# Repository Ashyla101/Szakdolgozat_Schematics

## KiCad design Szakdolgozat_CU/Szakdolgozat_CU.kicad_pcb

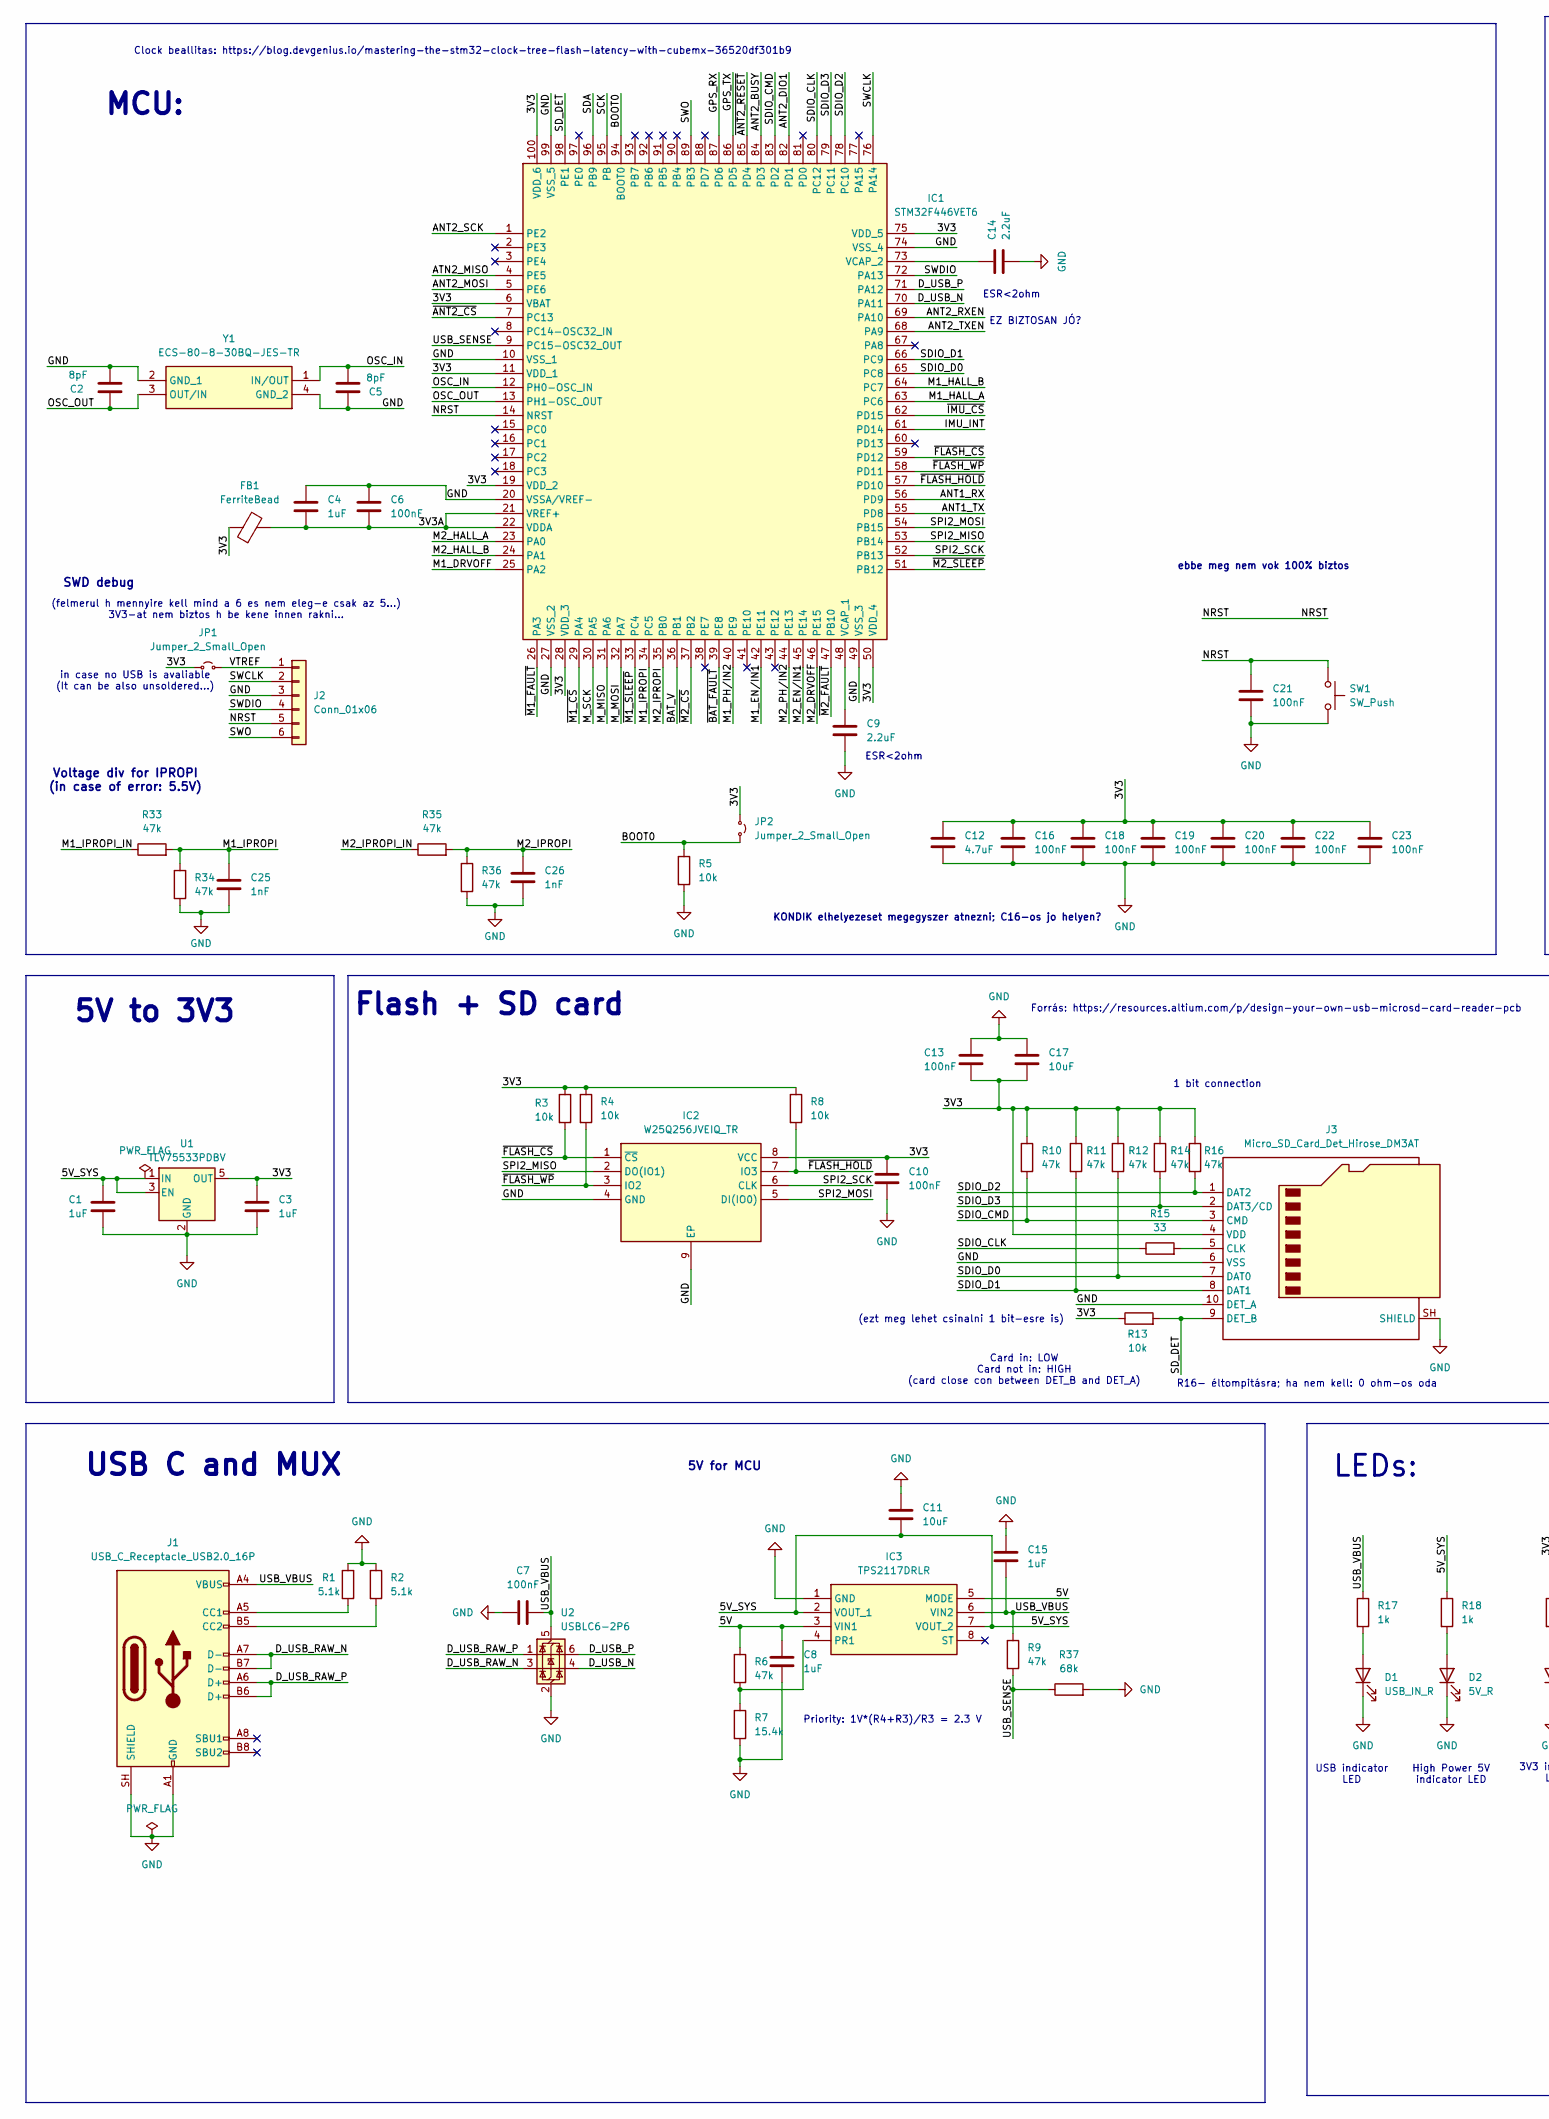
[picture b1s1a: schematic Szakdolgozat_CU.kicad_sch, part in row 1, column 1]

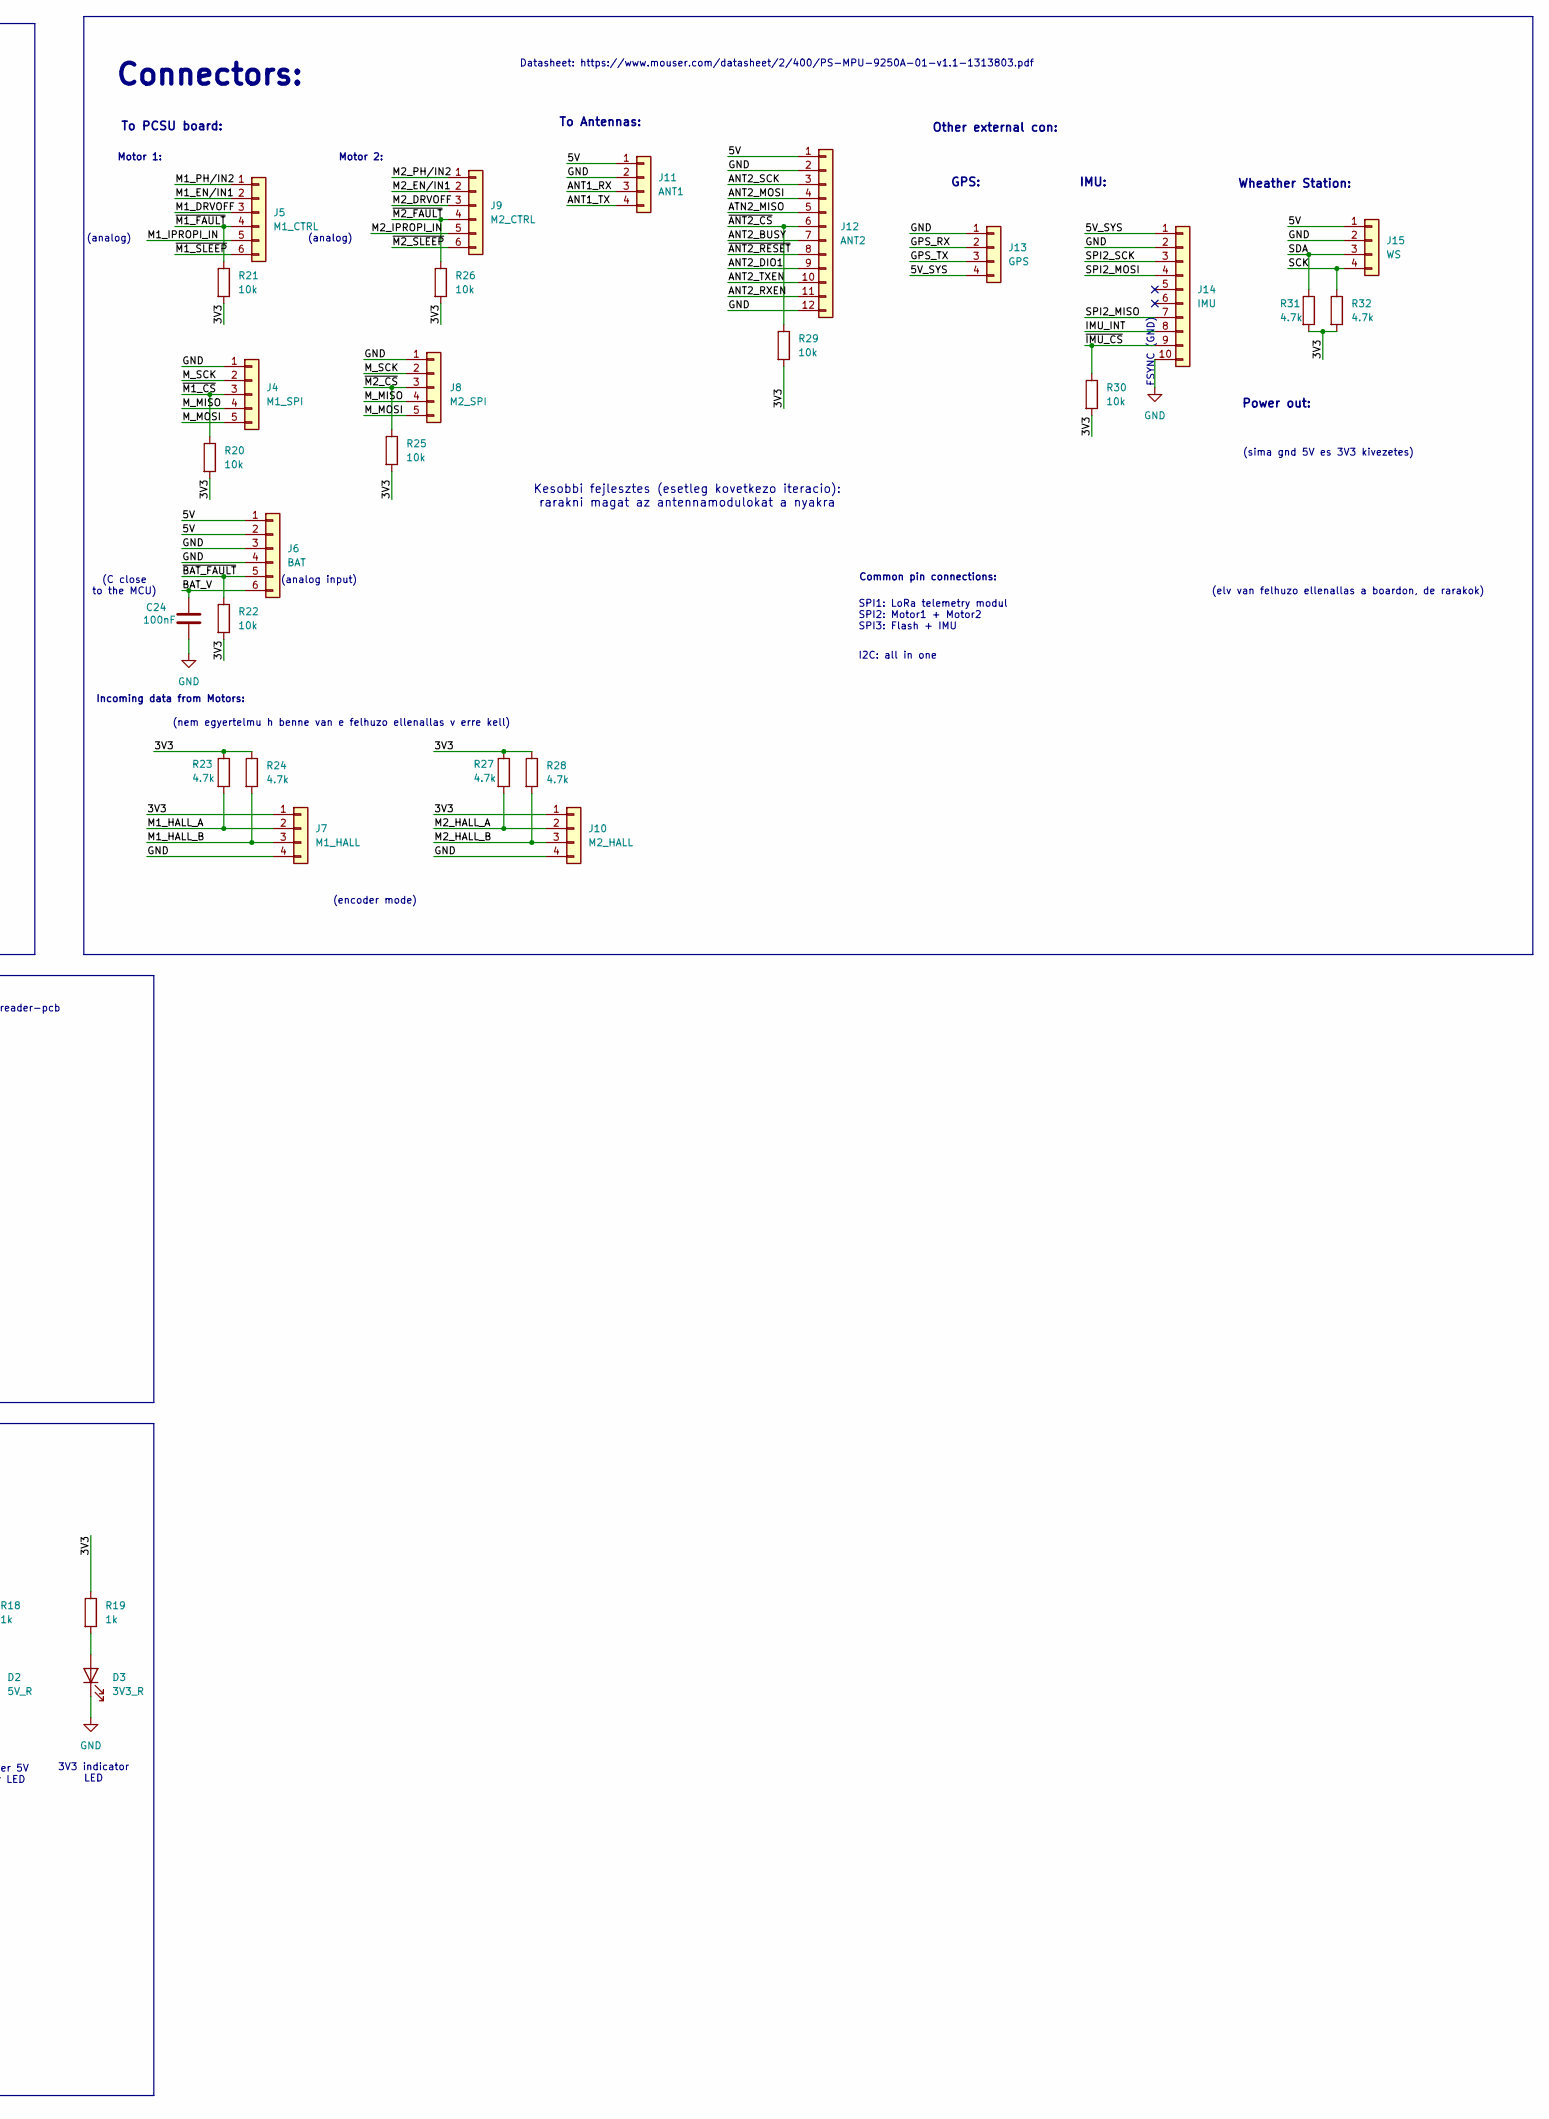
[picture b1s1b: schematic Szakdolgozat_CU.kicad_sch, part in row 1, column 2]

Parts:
C1, C3, C4, C8, C15: 1uF; C_0603_1608Metric_Pad1.08x0.95mm_HandSolder
C2, C5: 8pF; C_0603_1608Metric_Pad1.08x0.95mm_HandSolder
C6, C7, C10, C13, C16, C18, C19, C20, C21, C22, C23, C24: 100nF; C_0603_1608Metric_Pad1.08x0.95mm_HandSolder
C9, C14: 2.2uF; C_0603_1608Metric_Pad1.08x0.95mm_HandSolder
C11, C17: 10uF; C_0805_2012Metric_Pad1.18x1.45mm_HandSolder
C12: 4.7uF; C_0603_1608Metric_Pad1.08x0.95mm_HandSolder
C25, C26: 1nF; C_0603_1608Metric_Pad1.08x0.95mm_HandSolder
D1: USB_IN_R; LED_0603_1608Metric_Pad1.05x0.95mm_HandSolder
D2: 5V_R; LED_0603_1608Metric_Pad1.05x0.95mm_HandSolder
D3: 3V3_R; LED_0603_1608Metric_Pad1.05x0.95mm_HandSolder
FB1: FerriteBead; L_0603_1608Metric_Pad1.05x0.95mm_HandSolder
IC1: STM32F446VET6; QFP50P1600X1600X160-100N; Mouser Part Number 511-STM32F446VET6
IC2: W25Q256JVEIQ_TR; SON127P800X600X80-9N-D; Mouser Part Number 454-W25Q256JVEIQTR
IC3: TPS2117DRLR; SOTFL50P160X60-8N; Mouser Part Number 595-TPS2117DRLR
J1: USB_C_Receptacle_USB2.0_16P; USB_C_Receptacle_GCT_USB4105-xx-A_16P_TopMnt_Horizontal
J2: Conn_01x06; PinHeader_1x06_P2.54mm_Vertical
J3: Micro_SD_Card_Det_Hirose_DM3AT; microSD_HC_Hirose_DM3AT-SF-PEJM5
J4: M1_SPI; JST_XH_S5B-XH-A-1_1x05_P2.50mm_Horizontal
J5: M1_CTRL; JST_XH_S6B-XH-A-1_1x06_P2.50mm_Horizontal
J6: BAT; JST_XH_S6B-XH-A-1_1x06_P2.50mm_Horizontal
J7: M1_HALL; JST_XH_S4B-XH-A-1_1x04_P2.50mm_Horizontal
J8: M2_SPI; JST_XH_S5B-XH-A-1_1x05_P2.50mm_Horizontal
J9: M2_CTRL; JST_XH_S6B-XH-A-1_1x06_P2.50mm_Horizontal
J10: M2_HALL; JST_XH_S4B-XH-A-1_1x04_P2.50mm_Horizontal
J11: ANT1; JST_XH_S4B-XH-A-1_1x04_P2.50mm_Horizontal
J12: ANT2; JST_XH_S12B-XH-A-1_1x12_P2.50mm_Horizontal
J13: GPS; JST_XH_S4B-XH-A-1_1x04_P2.50mm_Horizontal
J14: IMU; JST_XH_S10B-XH-A_1x10_P2.50mm_Horizontal
J15: WS; JST_XH_S4B-XH-A-1_1x04_P2.50mm_Horizontal
JP1, JP2: Jumper_2_Small_Open; PinSocket_1x02_P2.54mm_Vertical
R1, R2: 5.1k; R_0603_1608Metric_Pad0.98x0.95mm_HandSolder
R3, R4, R5, R8, R13, R20, R21, R22, R25, R26, R29, R30: 10k; R_0603_1608Metric_Pad0.98x0.95mm_HandSolder
R6, R9, R10, R11, R12, R14, R16, R33, R34, R35, R36: 47k; R_0603_1608Metric_Pad0.98x0.95mm_HandSolder
R7: 15.4k; R_0603_1608Metric_Pad0.98x0.95mm_HandSolder
R15: 33; R_0603_1608Metric_Pad0.98x0.95mm_HandSolder
R17, R18, R19: 1k; R_0603_1608Metric_Pad0.98x0.95mm_HandSolder
R23, R24, R27, R28, R31, R32: 4.7k; R_0603_1608Metric_Pad0.98x0.95mm_HandSolder
R37: 68k; R_0603_1608Metric_Pad0.98x0.95mm_HandSolder
SW1: SW_Push; SW_Tactile_SPST_NO_Straight_CK_PTS636Sx25SMTRLFS
U1: TLV75533PDBV; SOT-23-5
U2: USBLC6-2P6; SOT-666
Y1: ECS-80-8-30BQ-JES-TR; ECS80830BQJESTR; Mouser Part Number 520-80-8-30BQ-JES-TR

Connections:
/3V3: C3.1, C10.1, C12.2, C13.2, C16.2, C17.2, C18.1, C19.1, C20.2, C22.2, C23.2, FB1.1, IC1.6 (VBAT), IC1.11 (VDD_1), IC1.19 (VDD_2), IC1.28 (VDD_3), IC1.50 (VDD_4), IC1.75 (VDD_5), IC1.100 (VDD_6), IC2.8 (VCC), J3.4 (VDD), J7.1, J10.1, JP1.1 (A), JP2.1 (A), R3.1, R4.1, R8.1, R10.1, R11.1, R12.1, R13.1, R14.1, R16.1, R19.1, R20.2, R21.2, R22.2, R23.1, R24.1, R25.2, R26.2, R27.1, R28.1, R29.2, R30.2, R31.2, R32.2, U1.5 (OUT)
/3V3A: C4.2, C6.2, FB1.2, IC1.21 (VREF+), IC1.22 (VDDA)
/5V: C8.1, IC3.3 (VIN1), IC3.5 (MODE), J6.1, J6.2, J11.1, J12.1, J15.1, R6.1
/5V_SYS: C1.1, C11.1, IC3.2 (VOUT_1), IC3.7 (VOUT_2), J13.4, J14.1, R18.1, U1.1 (IN), U1.3 (EN)
/ANT1_RX: IC1.56 (PD9), J11.3
/ANT1_TX: IC1.55 (PD8), J11.4
/ANT2_BUSY: IC1.84 (PD3), J12.7
/ANT2_DIO1: IC1.82 (PD1), J12.9
/ANT2_MOSI: IC1.5 (PE6), J12.4
/ANT2_RXEN: IC1.69 (PA10), J12.11
/ANT2_SCK: IC1.1 (PE2), J12.3
/ANT2_TXEN: IC1.68 (PA9), J12.10
/ATN2_MISO: IC1.4 (PE5), J12.5
/BAT_V: C24.1, IC1.36 (PB1), J6.6
/BOOT0: IC1.94 (BOOT0), JP2.2 (B), R5.1
/D_USB_N: IC1.70 (PA11), U2.4 (I/O2)
/D_USB_P: IC1.71 (PA12), U2.6 (I/O1)
/D_USB_RAW_N: J1.A7 (D-), J1.B7 (D-), U2.3 (I/O2)
/D_USB_RAW_P: J1.A6 (D+), J1.B6 (D+), U2.1 (I/O1)
/GPS_RX: IC1.87 (PD6), J13.2
/GPS_TX: IC1.86 (PD5), J13.3
/IMU_INT: IC1.61 (PD14), J14.8
/M1_DRVOFF: IC1.25 (PA2), J5.3
/M1_EN/IN1: IC1.42 (PE11), J5.2
/M1_HALL_A: IC1.63 (PC6), J7.2, R23.2
/M1_HALL_B: IC1.64 (PC7), J7.3, R24.2
/M1_IPROPI: C25.1, IC1.34 (PC5), R33.2, R34.2
/M1_IPROPI_IN: J5.5, R33.1
/M1_PH/IN2: IC1.40 (PE9), J5.1
/M2_DRVOFF: IC1.46 (PE15), J9.3
/M2_EN/IN1: IC1.45 (PE14), J9.2
/M2_HALL_A: IC1.23 (PA0), J10.2, R27.2
/M2_HALL_B: IC1.24 (PA1), J10.3, R28.2
/M2_IPROPI: C26.1, IC1.35 (PB0), R35.2, R36.1
/M2_IPROPI_IN: J9.5, R35.1
/M2_PH/IN2: IC1.44 (PE13), J9.1
/M_MISO: IC1.31 (PA6), J4.4, J8.4
/M_MOSI: IC1.32 (PA7), J4.5, J8.5
/M_SCK: IC1.30 (PA5), J4.2, J8.2
/NRST: C21.1, IC1.14 (NRST), J2.5, SW1.1
/OSC_IN: C5.2, IC1.12 (PH0-OSC_IN), Y1.1 (IN/OUT)
/OSC_OUT: C2.2, IC1.13 (PH1-OSC_OUT), Y1.3 (OUT/IN)
/SCK: IC1.95 (PB), J15.4, R32.1
/SDA: IC1.96 (PB9), J15.3, R31.1
/SDIO_CLK: IC1.80 (PC12), R15.1
/SDIO_CMD: IC1.83 (PD2), J3.3 (CMD), R10.2
/SDIO_D0: IC1.65 (PC8), J3.7 (DAT0), R12.2
/SDIO_D1: IC1.66 (PC9), J3.8 (DAT1), R11.2
/SDIO_D2: IC1.78 (PC10), J3.1 (DAT2), R16.2
/SDIO_D3: IC1.79 (PC11), J3.2 (DAT3/CD), R14.2
/SD_DET: IC1.98 (PE1), J3.9 (DET_B), R13.2
/SPI2_MISO: IC1.53 (PB14), IC2.2 (DO(IO1)), J14.7
/SPI2_MOSI: IC1.54 (PB15), IC2.5 (DI(IO0)), J14.4
/SPI2_SCK: IC1.52 (PB13), IC2.6 (CLK), J14.3
/SWCLK: IC1.76 (PA14), J2.2
/SWDIO: IC1.72 (PA13), J2.4
/SWO: IC1.89 (PB3), J2.6
/USB_SENSE: IC1.9 (PC15-OSC32_OUT), R9.2, R37.1
/USB_VBUS: C7.2, C15.2, IC3.6 (VIN2), J1.A4 (VBUS), J1.A9 (VBUS), J1.B4 (VBUS), J1.B9 (VBUS), R9.1, R17.1, U2.5 (VBUS)
/VTREF: J2.1, JP1.2 (B)
/~ANT2_CS: IC1.7 (PC13), J12.6, R29.1
/~ANT2_RESET: IC1.85 (PD4), J12.8
/~BAT_FAULT: IC1.39 (PE8), J6.5, R22.1
/~FLASH_CS: IC1.59 (PD12), IC2.1 (~CS), R3.2
/~FLASH_HOLD: IC1.57 (PD10), IC2.7 (IO3), R8.2
/~FLASH_WP: IC1.58 (PD11), IC2.3 (IO2), R4.2
/~IMU_CS: IC1.62 (PD15), J14.9, R30.1
/~M1_CS: IC1.29 (PA4), J4.3, R20.1
/~M1_FAULT: IC1.26 (PA3), J5.4, R21.1
/~M1_SLEEP: IC1.33 (PC4), J5.6
/~M2_CS: IC1.37 (PB2), J8.3, R25.1
/~M2_FAULT: IC1.47 (PB10), J9.4, R26.1
/~M2_SLEEP: IC1.51 (PB12), J9.6
GND: C1.2, C2.1, C3.2, C4.1, C5.1, C6.1, C7.1, C8.2, C9.1, C10.2, C11.2, C12.1, C13.1, C14.1, C15.1, C16.1, C17.1, C18.2, C19.2, C20.1, C21.2, C22.1, C23.1, C24.2, C25.2, C26.2, D1.1 (K), D2.1 (K), D3.1 (K), IC1.10 (VSS_1), IC1.20 (VSSA/VREF-), IC1.27 (VSS_2), IC1.49 (VSS_3), IC1.74 (VSS_4), IC1.99 (VSS_5), IC2.4 (GND), IC2.9 (EP), IC3.1 (GND), J1.A1 (GND), J1.A12 (GND), J1.B1 (GND), J1.B12 (GND), J1.SH (SHIELD), J2.3, J3.6 (VSS), J3.10 (DET_A), J3.SH (SHIELD), J4.1, J6.3, J6.4, J7.4, J8.1, J10.4, J11.2, J12.2, J12.12, J13.1, J14.2, J14.10, J15.2, R1.2, R2.1, R5.2, R7.2, R34.1, R36.2, R37.2, SW1.2, U1.2 (GND), U2.2 (GND), Y1.2 (GND_1), Y1.4 (GND_2)
unnamed: D1.2 (A), R17.2
unnamed: D2.2 (A), R18.2
unnamed: D3.2 (A), R19.2
unnamed: C9.2, IC1.48 (VCAP_1)
unnamed: C14.2, IC1.73 (VCAP_2)
unnamed: IC3.4 (PR1), R6.2, R7.1
unnamed: J1.A5 (CC1), R1.1
unnamed: J1.B5 (CC2), R2.2
unnamed: J3.5 (CLK), R15.2

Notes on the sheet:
Forrás: https://resources.altium.com/p/design-your-own-usb-microsd-card-reader-pcb
IMU:
Voltage div for IPROPI (in case of error: 5.5V)
Motor 1:
To Antennas:
Clock beallitas: https://blog.devgenius.io/mastering-the-stm32-clock-tree-flash-latency-with-cubemx-36520df301b9
Other external con:
Datasheet: https://www.mouser.com/datasheet/2/400/PS-MPU-9250A-01-v1.1-1313803.pdf
Wheather Station:
Incoming data from Motors:
USB indicator LED
(analog)
in case no USB is avaliable (It can be also unsoldered...)
EZ BIZTOSAN JÓ?
ESR<2ohm
Connectors:
SWD debug
USB C and MUX
(elv van felhuzo ellenallas a boardon, de rarakok)
FSYNC (GND)
MCU:
Priority: 1V*(R4+R3)/R3 = 2.3 V
GPS:
ebbe meg nem vok 100% biztos
R16- éltompitásra; ha nem kell: 0 ohm-os oda
KONDIK elhelyezeset megegyszer atnezni; C16-os jo helyen?
5V for MCU
Common pin connections:
Card in: LOW Card not in: HIGH (card close con between DET_B and DET_A)
Power out:
(C close to the MCU)
LEDs:
(sima gnd 5V es 3V3 kivezetes)
5V to 3V3
SPI1: LoRa telemetry modul SPI2: Motor1 + Motor2 SPI3: Flash + IMU
(encoder mode)
Motor 2:
(ezt meg lehet csinalni 1 bit-esre is)
I2C: all in one
(analog input)

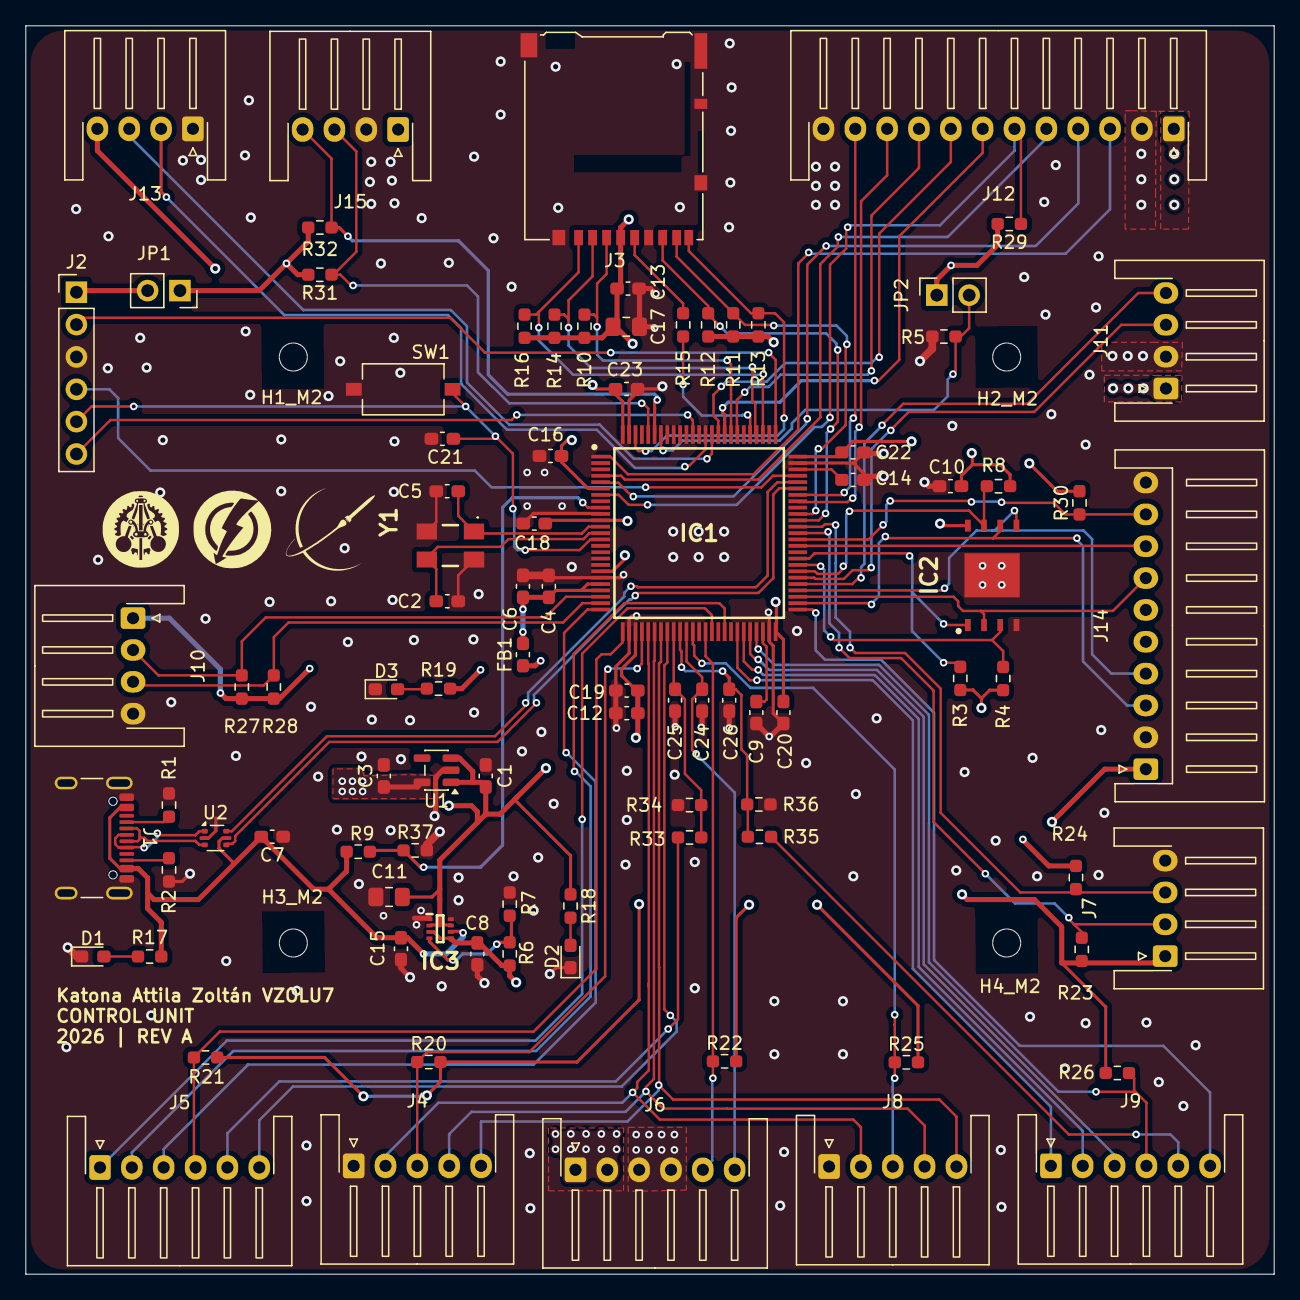
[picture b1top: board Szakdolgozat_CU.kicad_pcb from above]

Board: 4 copper layers, 98.0 x 98.0 mm, 95 parts (0 on the bottom side), 83 nets.

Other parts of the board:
H1_M2, H2_M2, H3_M2, H4_M2: MountingHole_2.2mm_M2

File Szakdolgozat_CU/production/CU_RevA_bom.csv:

Designator,Footprint,Quantity,Value,LCSC Part #
"C1, C15, C3, C4, C8",0603,5,1uF,
"C10, C13, C16, C18, C19, C20, C21, C22, C23, C24, C6, C7",0603,12,100nF,
"C11, C17",0805,2,10uF,
C12,0603,1,4.7uF,
"C14, C9",0603,2,2.2uF,
"C2, C5",0603,2,8pF,
"C25, C26",0603,2,1nF,
D1,0603,1,USB_IN_R,
D2,0603,1,5V_R,
D3,0603,1,3V3_R,
FB1,0603,1,FerriteBead,
IC1,QFP50P1600X1600X160-100N,1,STM32F446VET6,
IC2,SON127P800X600X80-9N-D,1,W25Q256JVEIQ_TR,
IC3,SOTFL50P160X60-8N,1,TPS2117DRLR,
J1,USB_C_Receptacle_GCT_USB4105-xx-A_16P_TopMnt_Horizontal,1,USB_C_Receptacle_USB2.0_16P,
J10,JST_XH_S4B-XH-A-1_1x04_P2.50mm_Horizontal,1,M2_HALL,
J11,JST_XH_S4B-XH-A-1_1x04_P2.50mm_Horizontal,1,ANT1,
J12,JST_XH_S12B-XH-A-1_1x12_P2.50mm_Horizontal,1,ANT2,
J13,JST_XH_S4B-XH-A-1_1x04_P2.50mm_Horizontal,1,GPS,
J14,JST_XH_S10B-XH-A_1x10_P2.50mm_Horizontal,1,IMU,
J15,JST_XH_S4B-XH-A-1_1x04_P2.50mm_Horizontal,1,WS,
J2,PinHeader_1x06_P2.54mm_Vertical,1,Conn_01x06,
J3,microSD_HC_Hirose_DM3AT-SF-PEJM5,1,Micro_SD_Card_Det_Hirose_DM3AT,
J4,JST_XH_S5B-XH-A-1_1x05_P2.50mm_Horizontal,1,M1_SPI,
J5,JST_XH_S6B-XH-A-1_1x06_P2.50mm_Horizontal,1,M1_CTRL,
J6,JST_XH_S6B-XH-A-1_1x06_P2.50mm_Horizontal,1,BAT,
J7,JST_XH_S4B-XH-A-1_1x04_P2.50mm_Horizontal,1,M1_HALL,
J8,JST_XH_S5B-XH-A-1_1x05_P2.50mm_Horizontal,1,M2_SPI,
J9,JST_XH_S6B-XH-A-1_1x06_P2.50mm_Horizontal,1,M2_CTRL,
"JP1, JP2",PinSocket_1x02_P2.54mm_Vertical,2,Jumper_2_Small_Open,
"R1, R2",0603,2,5.1k,
"R10, R11, R12, R14, R16, R33, R34, R35, R36, R6, R9",0603,11,47k,
"R13, R20, R21, R22, R25, R26, R29, R3, R30, R4, R5, R8",0603,12,10k,
R15,0603,1,33,
"R17, R18, R19",0603,3,1k,
"R23, R24, R27, R28, R31, R32",0603,6,4.7k,
R37,0603,1,68k,
R7,0603,1,15.4k,
SW1,SW_Tactile_SPST_NO_Straight_CK_PTS636Sx25SMTRLFS,1,SW_Push,
U1,SOT-23-5,1,TLV75533PDBV,
U2,SOT-666,1,USBLC6-2P6,
Y1,ECS80830BQJESTR,1,ECS-80-8-30BQ-JES-TR,
